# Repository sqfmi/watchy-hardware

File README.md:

# Watchy - Hardware Source Files

**Buy Watchy from [The Pi Hut](https://thepihut.com/collections/sqfmi), [Crowd Supply](https://www.crowdsupply.com/sqfmi/watchy), and [Mouser](https://www.mouser.com/ProductDetail/SQFMI/SQFMI-WATCHY-10?qs=DRkmTr78QARN9VSJRzqRxw%3D%3D)!**

[**Watchy Case & Accessories**](https://shop.sqfmi.com)

Visit [**https://watchy.sqfmi.com**](https://watchy.sqfmi.com) to get started!

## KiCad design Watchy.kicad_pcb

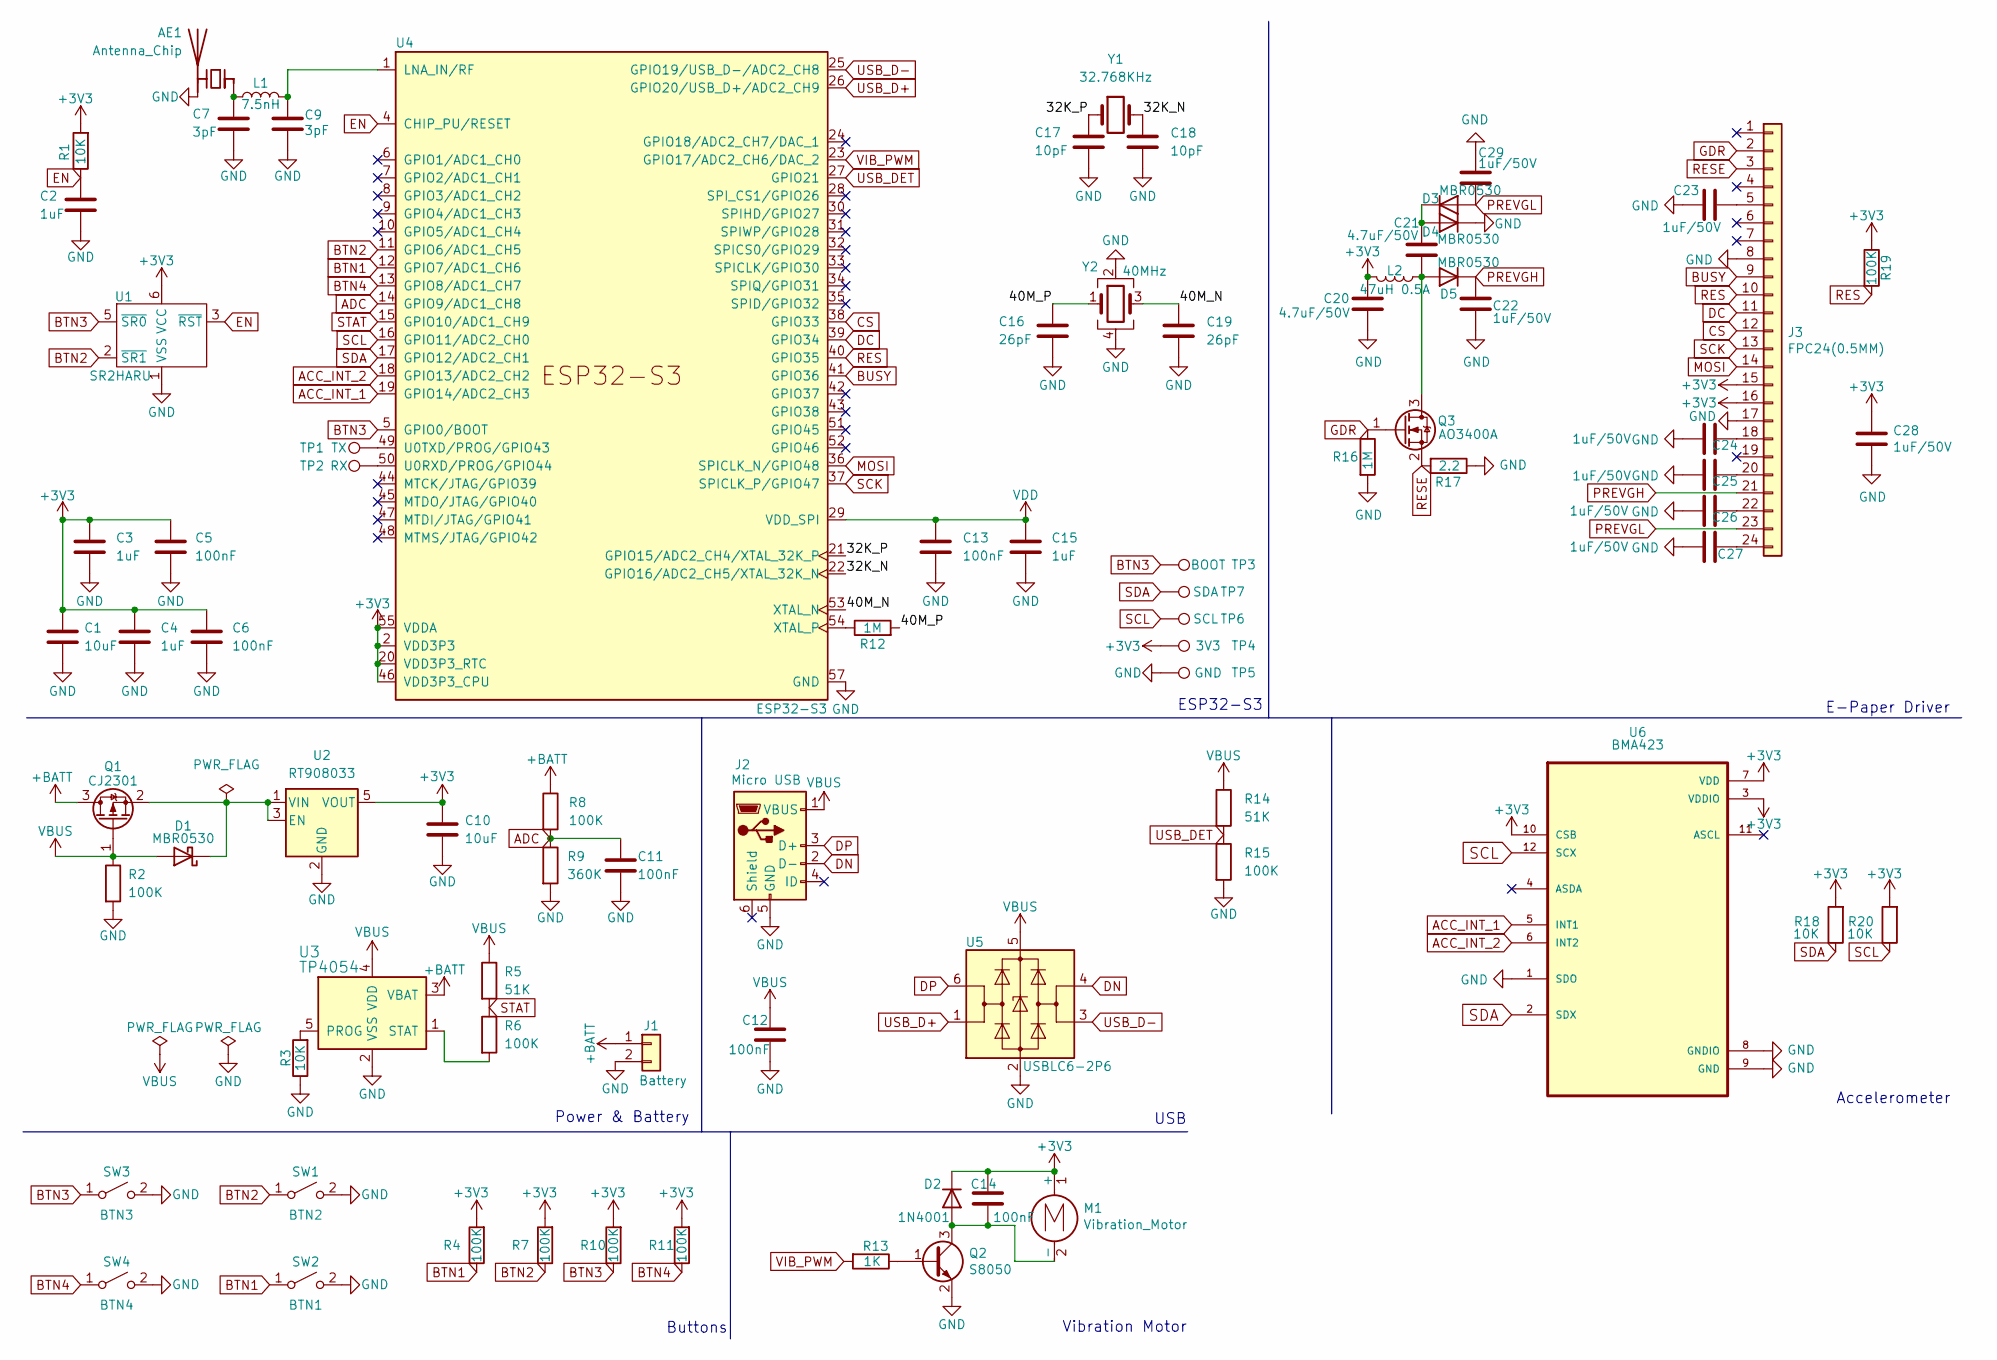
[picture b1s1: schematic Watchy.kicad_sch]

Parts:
AE1: Antenna_Chip; SWRA117D
C1, C10: 10uF; C_0402_1005Metric
C2, C3, C4, C15: 1uF; C_0402_1005Metric
C5, C6, C11, C12, C13, C14: 100nF; C_0402_1005Metric
C7, C9: 3pF; C_0402_1005Metric
C16, C19: 26pF; C_0402_1005Metric
C17, C18: 10pF; C_0402_1005Metric
C20, C21: 4.7uF/50V; C_0603_1608Metric
C22, C23, C24, C25, C26, C27, C28, C29: 1uF/50V; C_0402_1005Metric
D1, D3, D4, D5: MBR0530; D_SOD-123
D2: 1N4001; D_SOD-123F
J1: Battery; 1.25T-2PWT (Molex 532610271)
J2: Micro USB; USB_Micro-B
J3: FPC24(0.5MM); 24_Pins_0.5mm_Pitch_ZIF_Connector_UP
L1: 7.5nH; L_0402_1005Metric
L2: 47uH 0.5A; L_Taiyo-Yuden_NR-40xx
M1: Vibration_Motor; Motor_Header
Q1: CJ2301; SOT-23
Q2: S8050; SOT-23
Q3: AO3400A; SOT-23
R1, R3, R18, R20: 10K; R_0402_1005Metric
R2, R4, R6, R7, R8, R10, R11, R15, R19: 100K; R_0402_1005Metric
R5, R14: 51K; R_0402_1005Metric
R9: 360K; R_0402_1005Metric
R12, R16: 1M; R_0402_1005Metric
R13: 1K; R_0402_1005Metric
R17: 2.2; R_0402_1005Metric
SW1: BTN2; EVQPUC
SW2: BTN1; EVQPUC
SW3: BTN3; EVQPUC
SW4: BTN4; EVQPUC
TP1: TX; TestPoint_Pad_D1.0mm
TP2: RX; TestPoint_Pad_D1.0mm
TP3: BOOT; TestPoint_Pad_D1.0mm
TP4: 3V3; TestPoint_Pad_D1.0mm
TP5: GND; TestPoint_Pad_D1.0mm
TP6: SCL; TestPoint_Pad_D1.0mm
TP7: SDA; TestPoint_Pad_D1.0mm
U1: SR2HARU
U2: RT908033; SOT-23-5
U3: TP4054; SOT-23-5
U4: ESP32-S3; QFN-56-1EP_7x7mm_P0.4mm_EP5.6x5.6mm
U5: USBLC6-2P6; SOT-666
U6: BMA423; LGA-12_2x2mm_P0.5mm
Y1: 32.768KHz; Crystal_SMD_2012-2Pin_2.0x1.2mm
Y2: 40MHz; Crystal_SMD_2520-4Pin_2.5x2.0mm

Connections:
+3V3: C1.1, C3.1, C4.1, C5.1, C6.1, C10.1, C14.1, C20.1, C28.1, D2.1 (K), J3.15, J3.16, L2.2, M1.1 (+), R1.2, R4.2, R7.2, R10.2, R11.2, R18.2, R19.1, R20.2, TP4.1, U1.6 (VCC), U2.5 (VOUT), U4.2 (VDD3P3), U4.3 (VDD3P3), U4.20 (VDD3P3_RTC), U4.46 (VDD3P3_CPU), U4.55 (VDDA), U4.56 (VDDA), U6.3 (VDDIO), U6.7 (VDD), U6.10 (CSB); also elsewhere on the board
+BATT: J1.1, Q1.3 (D), R8.1, U3.3 (VBAT)
/32K_N: C18.1, U4.22 (GPIO16/ADC2_CH5/XTAL_32K_N), Y1.2
/32K_P: C17.1, U4.21 (GPIO15/ADC2_CH4/XTAL_32K_P), Y1.1
/40M_N: C19.1, U4.53 (XTAL_N), Y2.3
/40M_P: C16.1, R12.2, Y2.1
ACC_INT_1: U4.19 (GPIO14/ADC2_CH3), U6.5 (INT1)
ACC_INT_2: U4.18 (GPIO13/ADC2_CH2), U6.6 (INT2)
ADC: C11.1, R8.2, R9.1, U4.14 (GPIO9/ADC1_CH8)
BTN1: R4.1, SW2.1 (A), U4.12 (GPIO7/ADC1_CH6)
BTN2: R7.1, SW1.1 (A), U1.2 (~SR1), U4.11 (GPIO6/ADC1_CH5)
BTN3: R10.1, SW3.1 (A), TP3.1, U1.5 (~SR0), U4.5 (GPIO0/BOOT)
BTN4: R11.1, SW4.1 (A), U4.13 (GPIO8/ADC1_CH7)
BUSY: J3.9, U4.41 (GPIO36)
CS: J3.12, U4.38 (GPIO33)
DC: J3.11, U4.39 (GPIO34)
DN: J2.2 (D-), U5.4 (I/O2)
DP: J2.3 (D+), U5.6 (I/O1)
EN: C2.1, R1.1, U1.3 (~RST), U4.4 (CHIP_PU/RESET)
GDR: J3.2, Q3.1 (G), R16.1
GND: AE1.2 (PCB_Trace), C1.2, C2.2, C3.2, C4.2, C5.2, C6.2, C7.2, C9.2, C10.2, C11.2, C12.2, C13.2, C15.2, C16.2, C17.2, C18.2, C19.2, C20.2, C22.2, C23.2, C24.2, C25.2, C26.2, C27.2, C28.2, C29.1, D4.1 (K), J1.2, J2.5 (GND), J3.8, J3.17, Q2.2 (E), R2.2, R3.1, R9.2, R15.2, R16.2, R17.1, SW1.2 (B), SW2.2 (B), SW3.2 (B), SW4.2 (B), TP5.1, U1.1 (VSS), U2.2 (GND), U3.2 (VSS), U4.57 (GND), U5.2 (GND), U6.1 (SDO), U6.8 (GNDIO), U6.9 (GND), Y2.2, Y2.4; also elsewhere on the board
MOSI: J3.14, U4.36 (SPICLK_N/GPIO48)
unnamed: AE1.1 (FEED), C7.1, L1.1
unnamed: D1.1 (K), Q1.2 (S), U2.1 (VIN), U2.3 (EN)
unnamed: C14.2, D2.2 (A), M1.2 (-), Q2.3 (C)
unnamed: C21.1, D3.1 (K), D4.2 (A)
unnamed: C21.2, D5.2 (A), L2.1, Q3.3 (D)
unnamed: C23.1, J3.5
unnamed: C24.1, J3.18
unnamed: C25.1, J3.20
unnamed: C26.1, J3.22
unnamed: C27.1, J3.24
unnamed: Q2.1 (B), R13.1
unnamed: R3.2, U3.5 (PROG)
unnamed: R6.2, U3.1 (STAT)
unnamed: C9.1, L1.2, U4.1 (LNA_IN/RF)
unnamed: TP2.1, U4.50 (U0RXD/PROG/GPIO44)
unnamed: TP1.1, U4.49 (U0TXD/PROG/GPIO43)
unnamed: R12.1, U4.54 (XTAL_P)
PREVGH: C22.1, D5.1 (K), J3.21
PREVGL: C29.2, D3.2 (A), J3.23
RES: J3.10, R19.2, U4.40 (GPIO35)
RESE: J3.3, Q3.2 (S), R17.2
SCK: J3.13, U4.37 (SPICLK_P/GPIO47)
SCL: R20.1, TP6.1, U4.16 (GPIO11/ADC2_CH0), U6.12 (SCX)
SDA: R18.1, TP7.1, U4.17 (GPIO12/ADC2_CH1), U6.2 (SDX)
STAT: R5.2, R6.1, U4.15 (GPIO10/ADC1_CH9)
USB_D+: U4.26 (GPIO20/USB_D+/ADC2_CH9), U5.1 (I/O1)
USB_D-: U4.25 (GPIO19/USB_D-/ADC2_CH8), U5.3 (I/O2)
USB_DET: R14.2, R15.1, U4.27 (GPIO21)
VBUS: C12.1, D1.2 (A), J2.1 (VBUS), Q1.1 (G), R2.1, R5.1, R14.1, U3.4 (VDD), U5.5 (VBUS)
VDD: C13.1, C15.1, U4.29 (VDD_SPI)
VIB_PWM: R13.2, U4.23 (GPIO17/ADC2_CH6/DAC_2)

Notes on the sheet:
Vibration Motor
Buttons
E-Paper Driver
Accelerometer
ESP32-S3
USB
Power & Battery

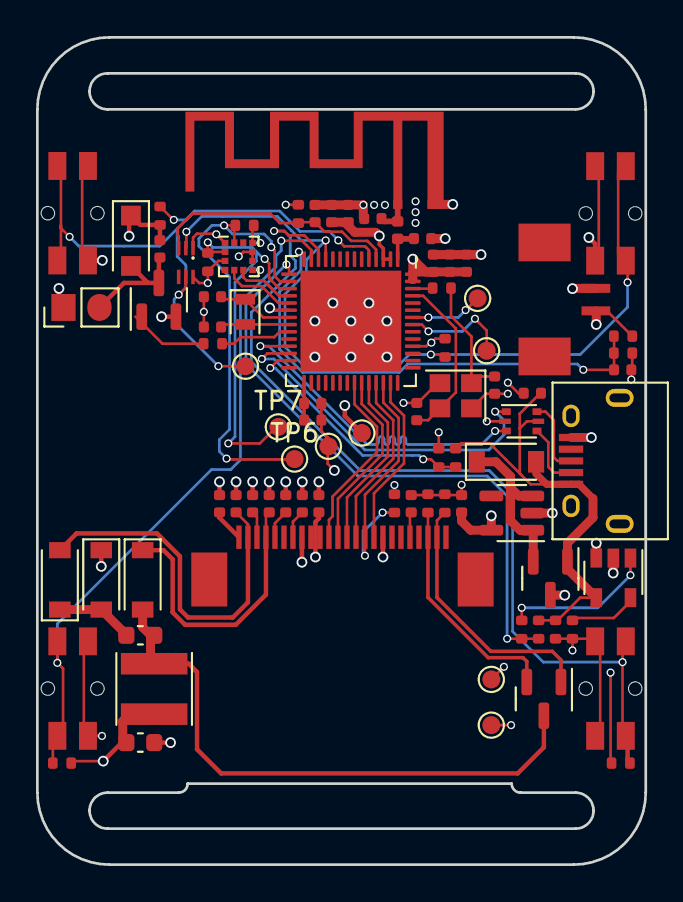
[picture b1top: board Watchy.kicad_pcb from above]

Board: 4 copper layers, 33.8 x 46.0 mm, 84 parts (0 on the bottom side), 53 nets.

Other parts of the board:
TP4#2: 3V3; TestPoint_Pad_D1.0mm
TP5#2: GND; TestPoint_Pad_D1.0mm

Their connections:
+3V3: TP4#2.1; also elsewhere on the board
GND: TP5#2.1; also elsewhere on the board

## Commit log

2020-12-20 Added KiCad Files
2020-12-31 added body step & STL
2020-12-31 added battery models
2021-05-27 added testpoints
2021-07-16 Add kitspace.yml
2021-12-25 v1.5
    - switched to new RTC (PCF8563)
2021-12-25 label CP2102
    CP2102
2022-04-03 v2.0
2024-07-24 Add v3 schematic
2026-01-31 Add files via upload
    file recovery
2026-01-31 Update LICENSE
